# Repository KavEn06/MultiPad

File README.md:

# MultiPad

## Features
- Triple layer 3D printed case
- 128x32 OLED Display
- EC11 Rotary encoder for volume and scrolling through other shortcut layers 
- 6 keys
- Very cool swirly design – trust me, it looks awesome in person

## CAD Model
The CAD model is held together with 4 M3 screws and heatset inserts. It’s built in three layers: the bottom layer holds all the components, the middle layer keeps the switches in place, and the top layer is mainly there to look nice.

Case            |  Layers
:-------------------------:|:-------------------------:
 | 

The CAD model was made in OnShape. 

## PCB 
Here's the PCB! It utilizes a XIAO RP2040, which is connected to 6 switches, a 128x32 OLED display, and an EC11 rotary encoder. 

Schematic            |  PCB
:-------------------------:|:-------------------------:
 | 

Since I'm the goat, I got 0 errors after I did the DRC check. 😎

## BOM:
Here is a list of everything you would need to build the MultiPad

- 6x Cherry MX Switches
- 6x DSA Keycaps
- 4x M3x5x4 Heatset inserts
- 2X M3x12mm Bolts
- 1x 0.91" 128x32 OLED Display
- 1x EC11 Rotary Encoder
- 1x XIAO RP2040
- 1x Case (3 3D printed parts)

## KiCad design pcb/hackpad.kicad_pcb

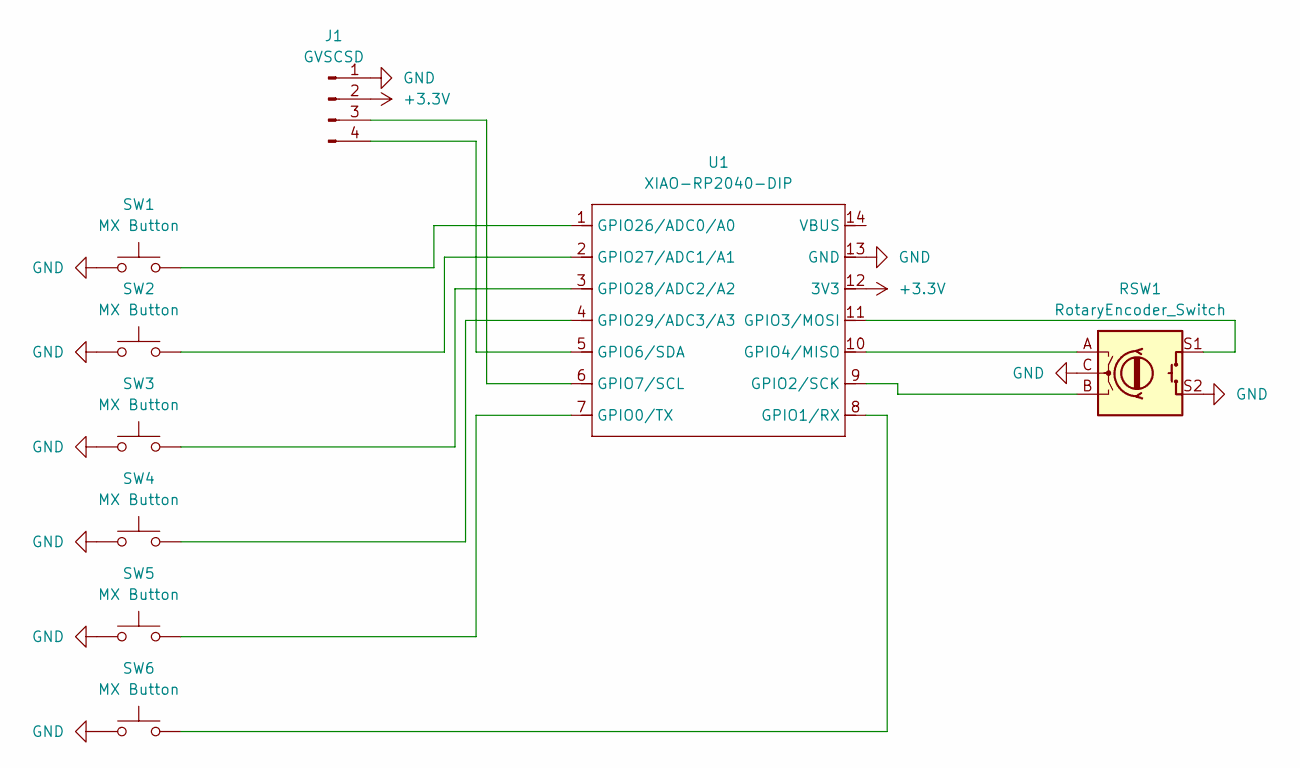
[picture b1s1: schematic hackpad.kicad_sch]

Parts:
J1: GVSCSD; SSD1306-0.91-OLED-4pin-128x32
RSW1: RotaryEncoder_Switch; RotaryEncoder_Alps_EC11E-Switch_Vertical_H20mm
SW1, SW2, SW3, SW4, SW5, SW6: MX Button; SW_Cherry_MX_1.00u_PCB
U1: XIAO-RP2040-DIP

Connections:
+3.3V: J1.2, U1.12 (3V3)
GND: J1.1, RSW1.C, RSW1.S2, SW1.1, SW2.1, SW3.1, SW4.1, SW5.1, SW6.1, U1.13 (GND)
unnamed: J1.3, U1.6 (GPIO7/SCL)
unnamed: J1.4, U1.5 (GPIO6/SDA)
unnamed: SW5.2, U1.7 (GPIO0/TX)
unnamed: SW6.2, U1.8 (GPIO1/RX)
unnamed: RSW1.B, U1.9 (GPIO2/SCK)
unnamed: RSW1.S1, U1.11 (GPIO3/MOSI)
unnamed: RSW1.A, U1.10 (GPIO4/MISO)
unnamed: SW1.2, U1.1 (GPIO26/ADC0/A0)
unnamed: SW2.2, U1.2 (GPIO27/ADC1/A1)
unnamed: SW3.2, U1.3 (GPIO28/ADC2/A2)
unnamed: SW4.2, U1.4 (GPIO29/ADC3/A3)

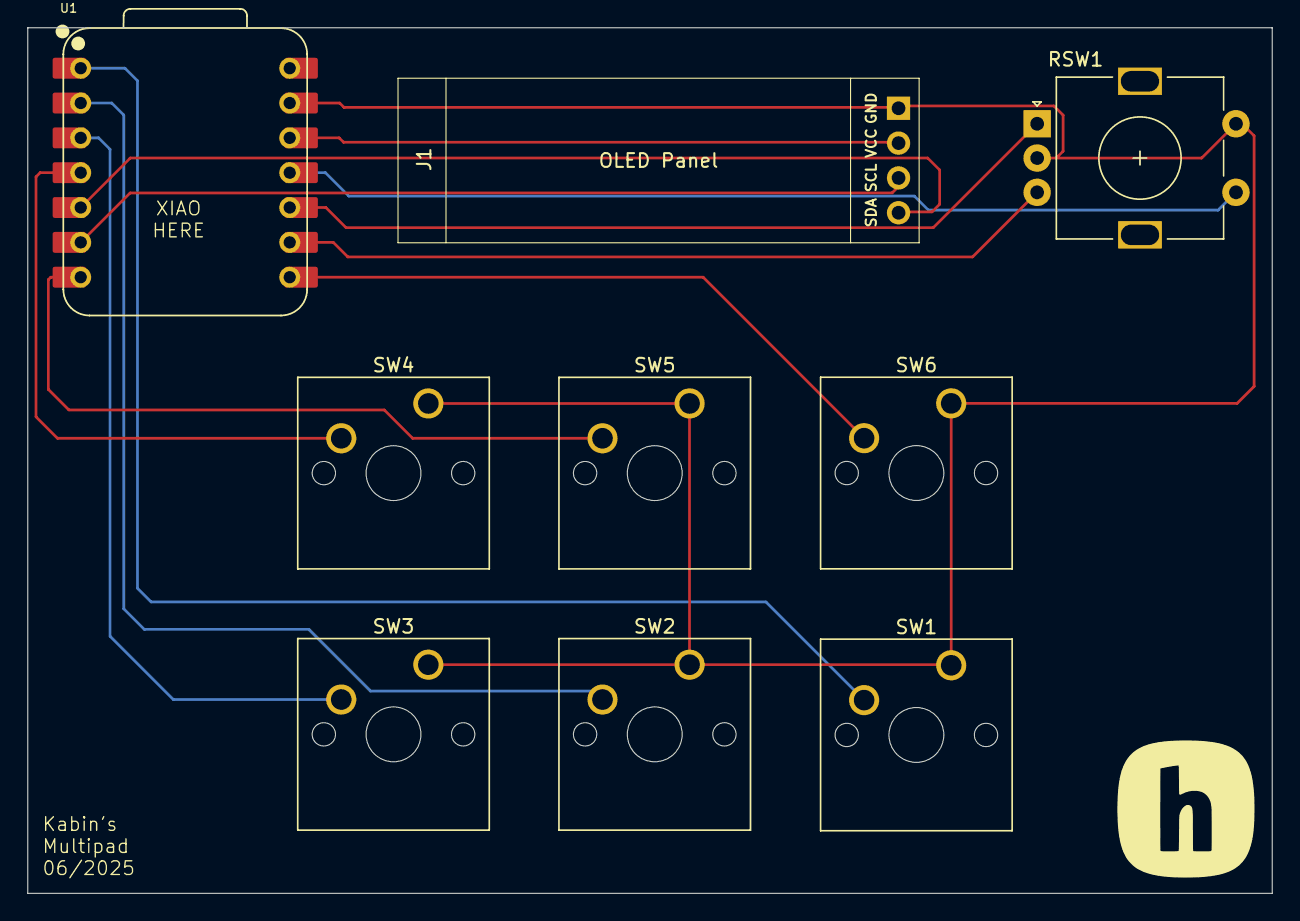
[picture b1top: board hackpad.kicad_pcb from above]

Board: 2 copper layers, 90.8 x 63.1 mm, 10 parts (0 on the bottom side), 13 nets.

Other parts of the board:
G: LOGO

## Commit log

2025-07-07 Create new
2025-07-07 added multipad v1 step
2025-07-07 added firmware code
2025-07-07 added firmware
2025-07-07 added stl files
2025-07-07 pcb files
2025-07-07 added gerber
